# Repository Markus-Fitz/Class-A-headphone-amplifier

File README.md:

# Class-A headphone amplifier
Simple class A headphone amplifier, made to be easy to build and understand while still sounding great.
The amplifier exclusively uses through-hole components, it doesn't use any integrated circuits and it uses standard values wherever possible.

## Design Philosophy

The amplifier is designed around a simple resistor-coupled class A output stage.
I like the appeal of the simplicity of resistor-coupled output stages and it allowed the amplifier to only have one high-power active device per channel which then could be displayed.
The power-transistor is an MJ2955, chosen for its TO-3 package which I really wanted to include as a center piece of the amplifier.
The transistor comes in one format, where its collector is connected to the case of the transistor. This, in combination with its place in the schematic allows it to have a grounded case, meaning it can be put on display on the outside of the case without any danger to the user.
Unfortunately, the MJ2955 struggles to keep up with fast rise- and fall-times, which led to problems outlined in the performance section.

Preceeding the output stage, a fully discrete pre-amplifier was created to keep THD at a minimum.
It is constructed like a discrete opAmp, with a differential input section and a voltage-amplification stage that then feeds the power-stage.

The output stage is connected to the amplifier's output through capacitive coupling and a delay-board. This delay board keeps the output of the capacitors connected to ground through resistors for the first ~4 seconds, allowing the output capacitors to slowly charge. This means that the output of the capacitors are at 0 V it connects to the headphones, which avoids a "thump" when turning the amplifier on.

To keep complexity at a minimum, the amplifier is powered from a single power supply of 24V, created by an external DC power-brick.
This was done to avoid working with line voltage, keeping the amplifier safe to operate and build up for hobbyists.
The input voltage is filtered by a passive power-supply. This, again, is a nod to vintage amplifier designs and was chosen for simplicity and to avoid having more power-semiconcutors in the regulation path of the power supply boards.

## Construction

As the amplifier is constructed from separate boards, a 3D printed case was designed to screw the boards onto one single frame.
From there, they could be connected to complete the amplifier.

The case additionally houses the power- and output-switches, a potentiometer for regulating the signal coming into the amplifier and connectors for the headphone, the inputs and preamp-outputs and the power-connector.

## Performance

The amplifier works as intended and amplifies the input signal properly. The sound is okay, but heavily compromised by massive noise coupling into the output signal.
This is probably due to the wiring on the bottom of the amplifier, which brings sensitive input audio signals in close proximity of large voltages and currents of the power-supply lines and output signals.
The 3D printed case does not shield the amplifier at all, meaning that even a mobile phone's RF pings were audible loudly.

The amplifier's output-stage is limited by the slow slew-rate capability of the MJ2955 transistor. This can even be seen in the simulations, as the preamp spikes to the positive supply voltage at fast positive edges on the input signal. The MJ2955 can not switch off as fast as the preamp-section commands it to, leading to the preamp to rise positive more and more. In the simulation, replacing the MJ2955 BJT by another BD140 solves this problem completely, indicating further that the MJ2955 is to blame.

Finally, the amplifier gets very hot during operation. Initially, a 500 mA bias current through the output stage was targeted, which would have meant a 22 Ohm power resistor in the output stage. The resistance was increased to 33 Ohms due to thermal concerns and even the 33 Ohm resistor (albeit only cooled convectively) gets far too hot to touch during operation.

All in all the amplifier shows a stable operation without any unexpected oscillations or other fatal flaws. The circuit works, but has weaknesses which make it impractical in a more refined setting after the prototype stage. For this reason, a next iteration may be modified quite extensively, on the basis of the present design.

## Next steps

To adress the noise issue, the next iteration will be build as one single PCB with a continuous ground plane.
A solid case constructed of metal will provide good cooling and shielding from interference from outside signals, allowing for quiet operation and keeping the case- and amplifier-temperature in a safe region.
A thermal safety switch or electronic NTC-control circuit may be implemented for furhter safety.
The output stage will omit the MJ2955 BJT and switch to a BD140. Additionally, the resistor-coupled output stage may be exchanged in favor of a current source or even transition to class AB for more power and cooler operation.
The power-supply will most likely laso be regulated. Without the MJ2955, the argument of having only one high-power semiconductor device is moot, so a simple regulator circuit may replace the hard-to-get and unprecise LC lowpass filter.

The amplifier will still be fully discrete, fully thorugh-hole mounted and fully open-source. I really want to create something which is usable every day though and the steps above feel adequate for that.

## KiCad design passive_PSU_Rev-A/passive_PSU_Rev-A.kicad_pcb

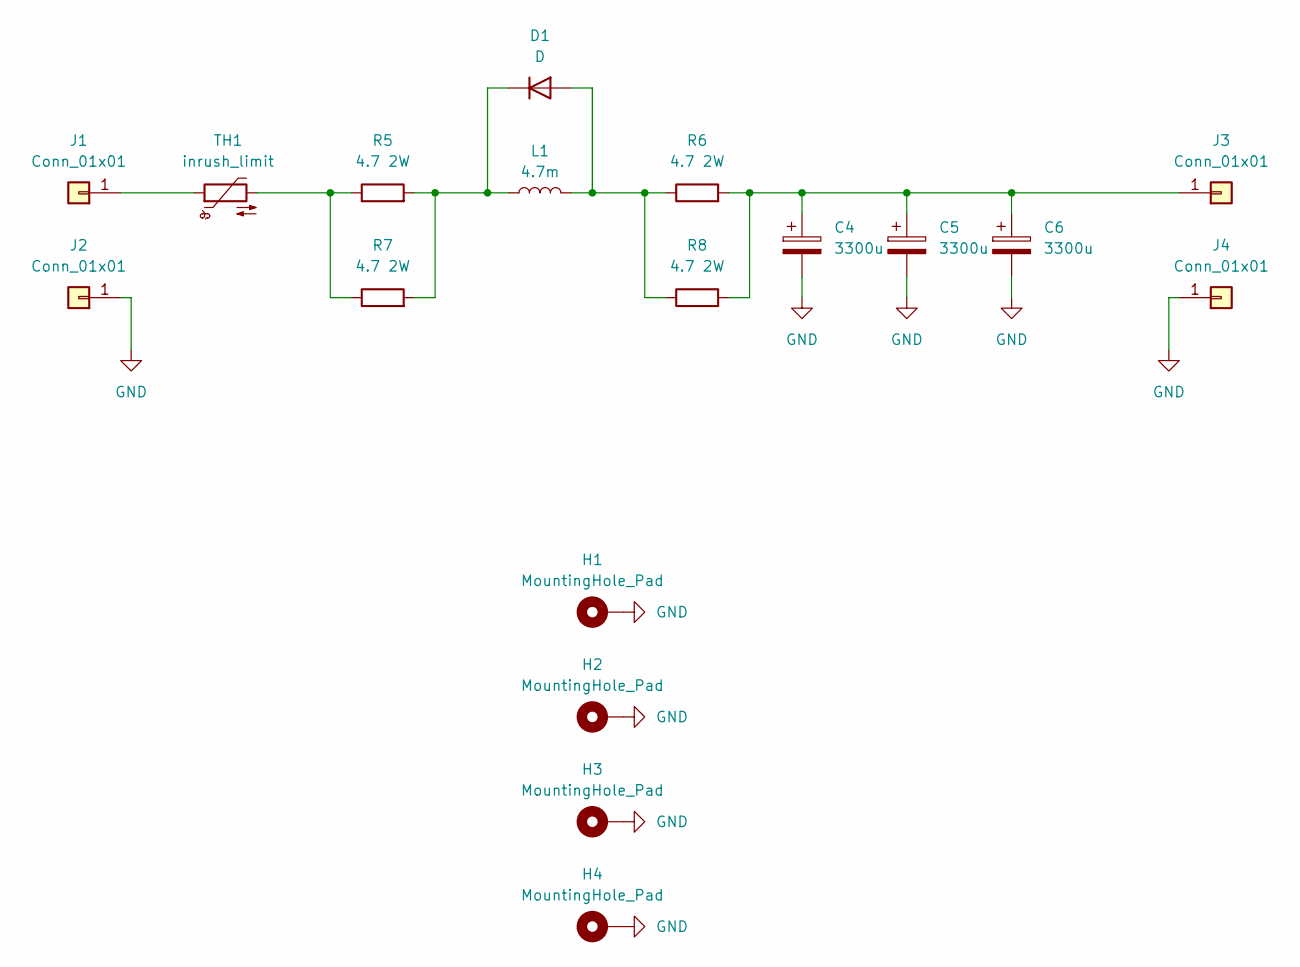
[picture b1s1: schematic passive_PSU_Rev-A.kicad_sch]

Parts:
C4, C5, C6: 3300u; CP_Radial_D16.0mm_P7.50mm; MPN UFW1V332MHD
D1: D; D_DO-27_P12.70mm_Horizontal
H1, H2, H3, H4: MountingHole_Pad; MountingHole_3.2mm_M3_DIN965_Pad_TopBottom
J1, J2, J3, J4: Conn_01x01; TestPoint_THTPad_D3.0mm_Drill1.5mm
L1: 4.7m; L_Radial_D24.4mm_P22.90mm_Murata_1400series
R5, R6, R7, R8: 4.7 2W; R_Axial_DIN0309_L9.0mm_D3.2mm_P12.70mm_Horizontal; MPN WA83ZI-4R7JT06
TH1: inrush_limit; C_Disc_D9.0mm_W5.0mm_P5.00mm; MPN B57153S0100M054

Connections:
GND: C4.2, C5.2, C6.2, H1.1, H2.1, H3.1, H4.1, J2.1, J4.1
unnamed: D1.2 (A), L1.2, R6.1, R8.1
unnamed: D1.1 (K), L1.1, R5.2, R7.2
unnamed: J1.1, TH1.1
unnamed: C4.1, C5.1, C6.1, J3.1, R6.2, R8.2
unnamed: R5.1, R7.1, TH1.2

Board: 2 copper layers, 18 parts (0 on the bottom side), 6 nets, no tracks yet.

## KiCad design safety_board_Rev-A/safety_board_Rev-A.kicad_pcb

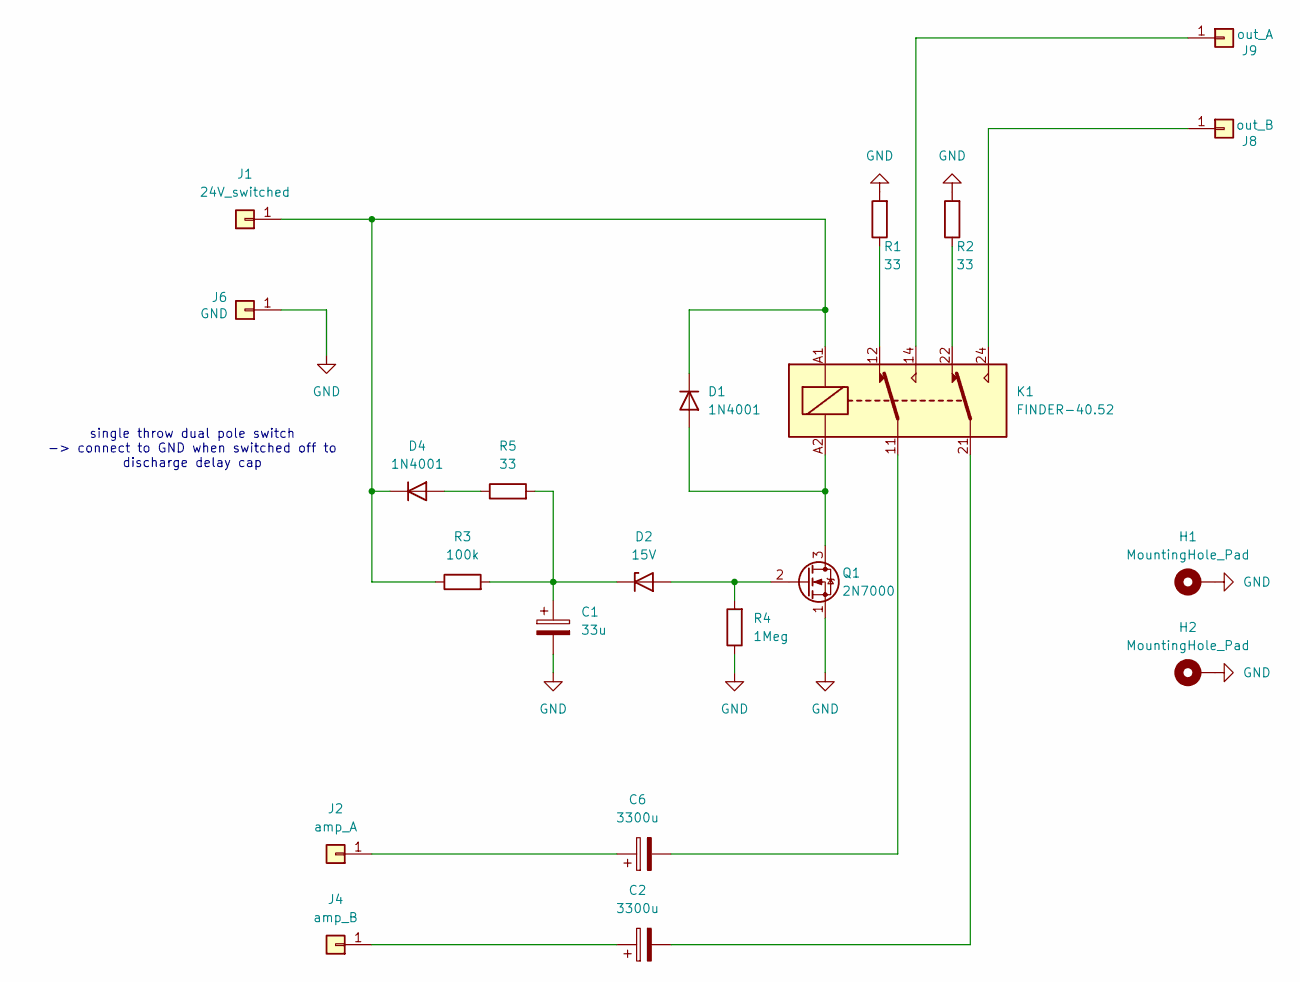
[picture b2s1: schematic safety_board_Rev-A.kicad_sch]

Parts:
C1: 33u; C_Radial_D8.0mm_H11.5mm_P3.50mm
C2, C6: 3300u; CP_Radial_D16.0mm_P7.50mm; MPN UFW1V332MHD
D1, D4: 1N4001; D_DO-41_SOD81_P10.16mm_Horizontal
D2: 15V; D_DO-35_SOD27_P7.62mm_Horizontal
H1, H2: MountingHole_Pad; MountingHole_3.2mm_M3_DIN965_Pad_TopBottom
J1: 24V_switched; TestPoint_THTPad_D3.0mm_Drill1.5mm
J2: amp_A; TestPoint_THTPad_D3.0mm_Drill1.5mm
J4: amp_B; TestPoint_THTPad_D3.0mm_Drill1.5mm
J6: GND; TestPoint_THTPad_D3.0mm_Drill1.5mm
J8: out_B; TestPoint_THTPad_D3.0mm_Drill1.5mm
J9: out_A; TestPoint_THTPad_D3.0mm_Drill1.5mm
K1: FINDER-40.52; Relay_DPDT_Finder_40.52
Q1: 2N7000; TO-92_Inline
R1, R2, R5: 33; R_Axial_DIN0207_L6.3mm_D2.5mm_P10.16mm_Horizontal
R3: 100k; R_Axial_DIN0207_L6.3mm_D2.5mm_P10.16mm_Horizontal
R4: 1Meg; R_Axial_DIN0207_L6.3mm_D2.5mm_P10.16mm_Horizontal

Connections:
GND: C1.2, H1.1, H2.1, J6.1, Q1.1 (S), R1.2, R2.2, R4.1
unnamed: C2.2, K1.21
unnamed: C6.2, K1.11
unnamed: D1.2 (A), K1.A2, Q1.3 (D)
unnamed: D1.1 (K), D4.1 (K), J1.1, K1.A1, R3.1
unnamed: D2.2 (A), Q1.2 (G), R4.2
unnamed: C1.1, D2.1 (K), R3.2, R5.2
unnamed: D4.2 (A), R5.1
unnamed: C6.1, J2.1
unnamed: C2.1, J4.1
unnamed: J8.1, K1.24
unnamed: J9.1, K1.14
unnamed: K1.12, R1.1
unnamed: K1.22, R2.1

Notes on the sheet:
single throw dual pole switch -> connect to GND when switched off to discharge delay cap

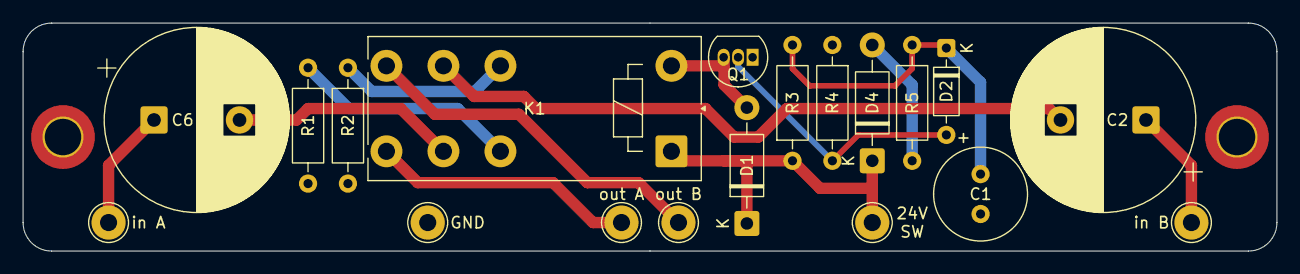
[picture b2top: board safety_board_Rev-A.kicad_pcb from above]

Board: 2 copper layers, 110.0 x 20.0 mm, 21 parts (0 on the bottom side), 14 nets.

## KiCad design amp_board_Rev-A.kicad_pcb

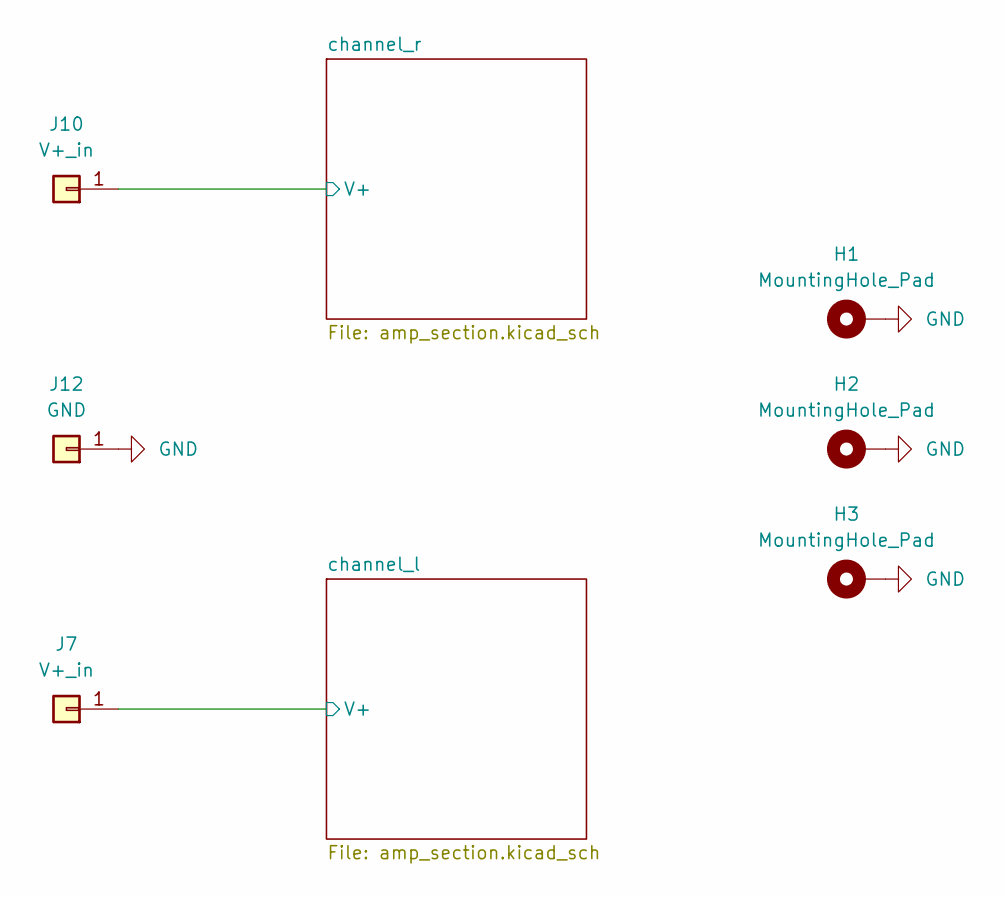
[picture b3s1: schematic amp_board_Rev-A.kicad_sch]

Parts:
H1, H2, H3: MountingHole_Pad; MountingHole_3.2mm_M3_DIN965_Pad_TopBottom
J7, J10: V+_in; TestPoint_THTPad_D3.0mm_Drill1.5mm
J12: GND; TestPoint_THTPad_D3.0mm_Drill1.5mm

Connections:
/channel_l/V+: J7.1; also elsewhere on the board
/channel_r/V+: J10.1; also elsewhere on the board
GND: H1.1, H2.1, H3.1, J12.1; also elsewhere on the board

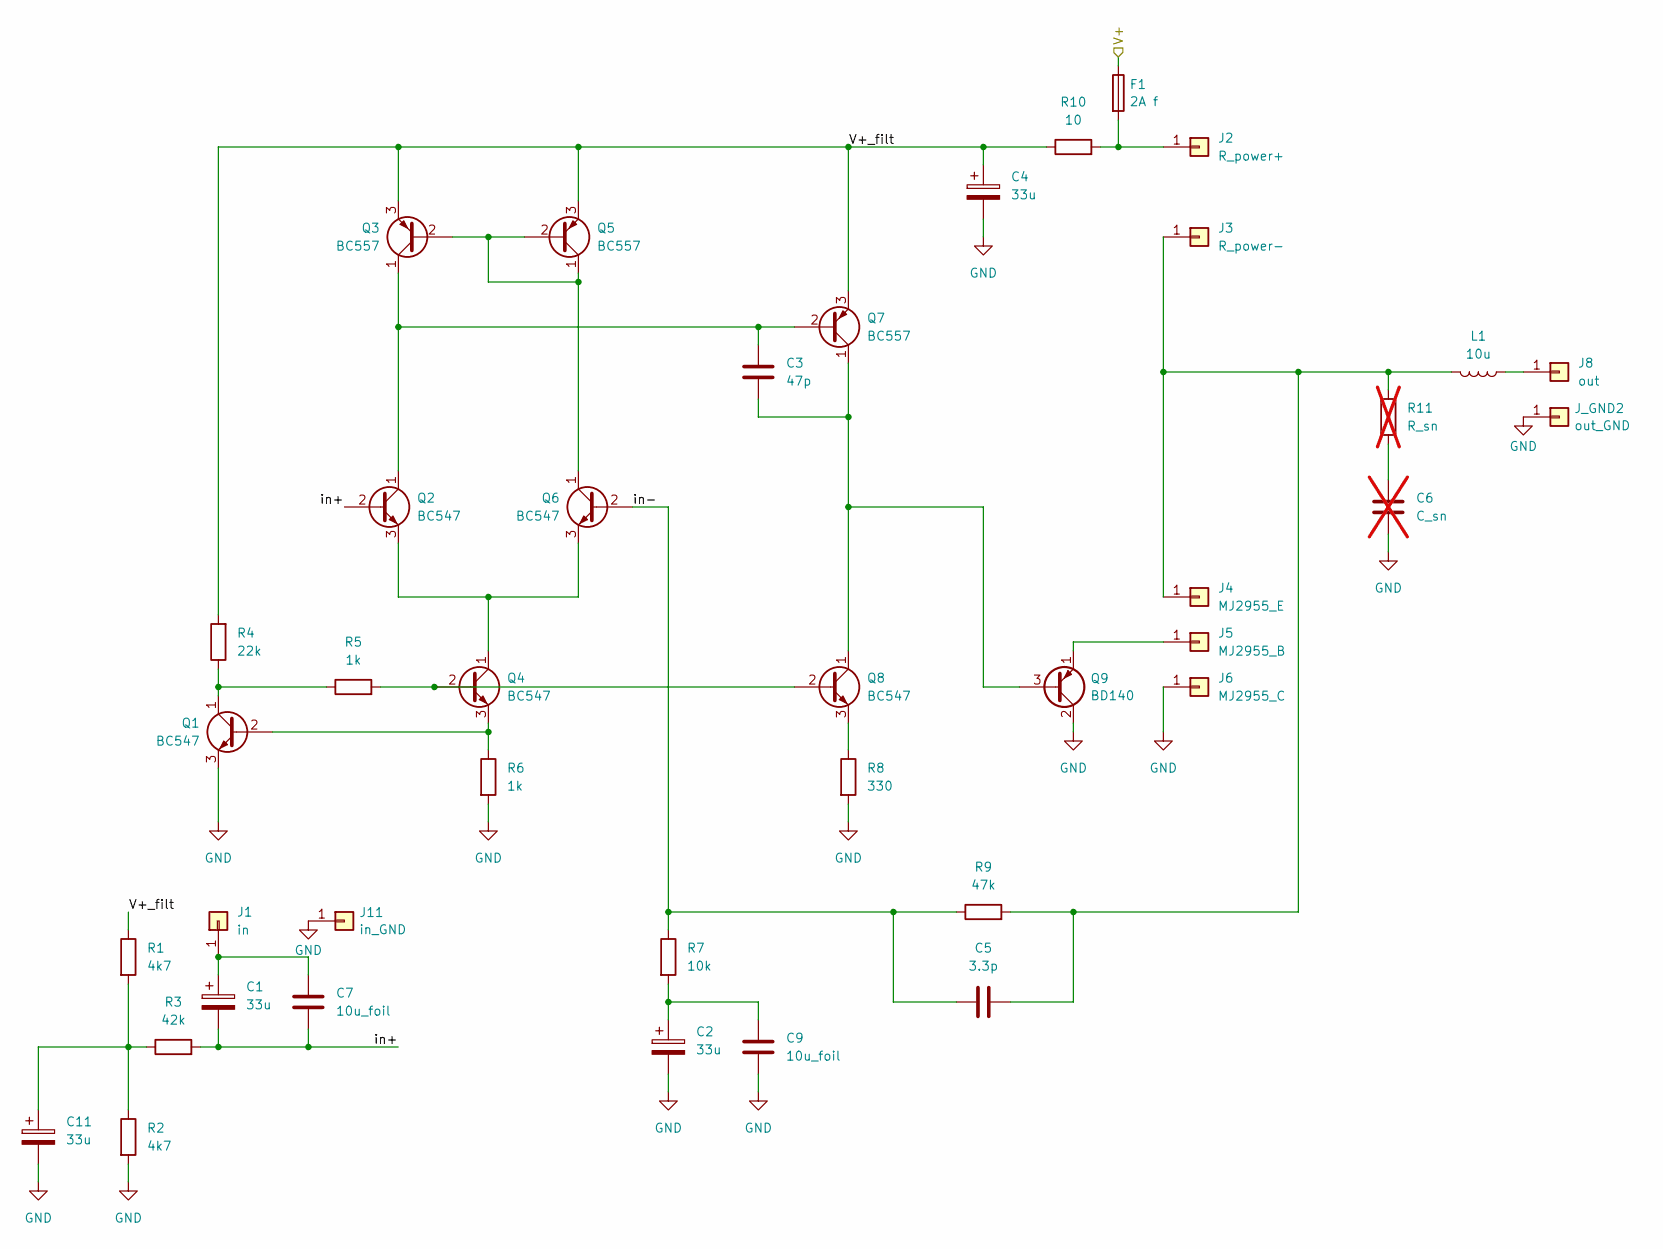
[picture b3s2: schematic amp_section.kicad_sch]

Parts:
C1, C2, C4, C11: 33u; C_Radial_D8.0mm_H11.5mm_P3.50mm
C3: 47p; C_Disc_D5.0mm_W2.5mm_P5.00mm
C5: 3.3p; C_Disc_D5.0mm_W2.5mm_P5.00mm
C6: C_sn; C_Disc_D5.0mm_W2.5mm_P5.00mm; not fitted
C7, C9: 10u_foil; C_Rect_L24.0mm_W10.9mm_P22.50mm_MKT
F1: 2A f; Fuseholder_Clip-5x20mm_Keystone_3512P_Inline_P23.62x7.27mm_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
J1: in; TestPoint_THTPad_D3.0mm_Drill1.5mm
J2: R_power+; TestPoint_THTPad_D3.0mm_Drill1.5mm
J3: R_power-; TestPoint_THTPad_D3.0mm_Drill1.5mm
J4: MJ2955_E; TestPoint_THTPad_D3.0mm_Drill1.5mm
J5: MJ2955_B; TestPoint_THTPad_D3.0mm_Drill1.5mm
J6: MJ2955_C; TestPoint_THTPad_D3.0mm_Drill1.5mm
J8: out; TestPoint_THTPad_D3.0mm_Drill1.5mm
J11: in_GND; TestPoint_THTPad_D3.0mm_Drill1.5mm
J_GND2: out_GND; TestPoint_THTPad_D3.0mm_Drill1.5mm
L1: 10u; L_Axial_L11.0mm_D4.5mm_P5.08mm_Vertical_Fastron_MECC
Q1, Q2, Q4, Q6, Q8: BC547; TO-92_Inline_Wide
Q3, Q5, Q7: BC557; TO-92_Inline_Wide
Q9: BD140; TO-126-3_Vertical
R1, R2: 4k7; R_Axial_DIN0207_L6.3mm_D2.5mm_P10.16mm_Horizontal
R3: 42k; R_Axial_DIN0207_L6.3mm_D2.5mm_P10.16mm_Horizontal
R4: 22k; R_Axial_DIN0207_L6.3mm_D2.5mm_P10.16mm_Horizontal
R5, R6: 1k; R_Axial_DIN0207_L6.3mm_D2.5mm_P10.16mm_Horizontal
R7: 10k; R_Axial_DIN0207_L6.3mm_D2.5mm_P10.16mm_Horizontal
R8: 330; R_Axial_DIN0207_L6.3mm_D2.5mm_P10.16mm_Horizontal
R9: 47k; R_Axial_DIN0207_L6.3mm_D2.5mm_P10.16mm_Horizontal
R10: 10; R_Axial_DIN0207_L6.3mm_D2.5mm_P10.16mm_Horizontal
R11: R_sn; R_Axial_DIN0207_L6.3mm_D2.5mm_P10.16mm_Horizontal; not fitted

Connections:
/channel_r/V+: F1.1; also elsewhere on the board
/channel_r/V+_filt: C4.1, Q3.3 (E), Q5.3 (E), Q7.3 (E), R1.1, R4.2, R10.1
/channel_r/in+: C1.2, C7.2, Q2.2 (B), R3.2
/channel_r/in-: C5.1, Q6.2 (B), R7.1, R9.1
GND: C2.2, C4.2, C6.2, C9.2, C11.2, J6.1, J11.1, J_GND2.1, Q1.3 (E), Q9.2 (C), R2.2, R6.2, R8.2; also elsewhere on the board
unnamed: C2.1, C9.1, R7.2
unnamed: C6.1, R11.2
unnamed: C11.1, R1.2, R2.1, R3.1
unnamed: C1.1, C7.1, J1.1
unnamed: F1.2, J2.1, R10.2
unnamed: C5.2, J3.1, J4.1, L1.2, R9.2, R11.1
unnamed: J5.1, Q9.1 (E)
unnamed: J8.1, L1.1
unnamed: Q1.2 (B), Q4.3 (E), R6.1
unnamed: Q1.1 (C), R4.1, R5.1
unnamed: C3.1, Q2.1 (C), Q3.1 (C), Q7.2 (B)
unnamed: Q2.3 (E), Q4.1 (C), Q6.3 (E)
unnamed: Q3.2 (B), Q5.1 (C), Q5.2 (B), Q6.1 (C)
unnamed: Q4.2 (B), Q8.2 (B), R5.2
unnamed: C3.2, Q7.1 (C), Q8.1 (C), Q9.3 (B)
unnamed: Q8.3 (E), R8.1

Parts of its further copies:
C8, C10: 10u_foil; C_Rect_L24.0mm_W10.9mm_P22.50mm_MKT
C12, C13, C14, C16: 33u; C_Radial_D8.0mm_H11.5mm_P3.50mm
C15: 47p; C_Disc_D5.0mm_W2.5mm_P5.00mm
C17: 3.3p; C_Disc_D5.0mm_W2.5mm_P5.00mm
C18: C_sn; C_Disc_D5.0mm_W2.5mm_P5.00mm; not fitted
F2: 2A f; Fuseholder_Clip-5x20mm_Keystone_3512P_Inline_P23.62x7.27mm_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
J_B1: MJ2955_B; TestPoint_THTPad_D3.0mm_Drill1.5mm
J_C1: MJ2955_C; TestPoint_THTPad_D3.0mm_Drill1.5mm
J_E1: MJ2955_E; TestPoint_THTPad_D3.0mm_Drill1.5mm
J_GND1: in_GND; TestPoint_THTPad_D3.0mm_Drill1.5mm
J_GND3: out_GND; TestPoint_THTPad_D3.0mm_Drill1.5mm
J_R+1: R_power+; TestPoint_THTPad_D3.0mm_Drill1.5mm
J_R-1: R_power-; TestPoint_THTPad_D3.0mm_Drill1.5mm
J_in1: in; TestPoint_THTPad_D3.0mm_Drill1.5mm
J_out1: out; TestPoint_THTPad_D3.0mm_Drill1.5mm
L3: 10u; L_Axial_L11.0mm_D4.5mm_P5.08mm_Vertical_Fastron_MECC
Q10: BD140; TO-126-3_Vertical
Q19, Q20, Q22, Q24, Q26: BC547; TO-92_Inline_Wide
Q21, Q23, Q25: BC557; TO-92_Inline_Wide
R23, R24: 4k7; R_Axial_DIN0207_L6.3mm_D2.5mm_P10.16mm_Horizontal
R25: 42k; R_Axial_DIN0207_L6.3mm_D2.5mm_P10.16mm_Horizontal
R26: 22k; R_Axial_DIN0207_L6.3mm_D2.5mm_P10.16mm_Horizontal
R27, R28: 1k; R_Axial_DIN0207_L6.3mm_D2.5mm_P10.16mm_Horizontal
R29: 10k; R_Axial_DIN0207_L6.3mm_D2.5mm_P10.16mm_Horizontal
R30: 330; R_Axial_DIN0207_L6.3mm_D2.5mm_P10.16mm_Horizontal
R31: 47k; R_Axial_DIN0207_L6.3mm_D2.5mm_P10.16mm_Horizontal
R32: 10; R_Axial_DIN0207_L6.3mm_D2.5mm_P10.16mm_Horizontal
R33: R_sn; R_Axial_DIN0207_L6.3mm_D2.5mm_P10.16mm_Horizontal; not fitted

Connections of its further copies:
/channel_l/V+: F2.1; also elsewhere on the board
/channel_l/V+_filt: C16.1, Q21.3 (E), Q23.3 (E), Q25.3 (E), R23.1, R26.2, R32.1
/channel_l/in+: C8.2, C13.2, Q20.2 (B), R25.2
/channel_l/in-: C17.1, Q24.2 (B), R29.1, R31.1
GND: C10.2, C12.2, C14.2, C16.2, C18.2, J_C1.1, J_GND1.1, J_GND3.1, Q10.2 (C), Q19.3 (E), R24.2, R28.2, R30.2; also elsewhere on the board
unnamed: C10.1, C14.1, R29.2
unnamed: C12.1, R23.2, R24.1, R25.1
unnamed: C18.1, R33.2
unnamed: J_B1.1, Q10.1 (E)
unnamed: C17.2, J_E1.1, J_R-1.1, L3.2, R31.2, R33.1
unnamed: F2.2, J_R+1.1, R32.2
unnamed: C8.1, C13.1, J_in1.1
unnamed: J_out1.1, L3.1
unnamed: C15.2, Q10.3 (B), Q25.1 (C), Q26.1 (C)
unnamed: Q19.2 (B), Q22.3 (E), R28.1
unnamed: Q19.1 (C), R26.1, R27.1
unnamed: C15.1, Q20.1 (C), Q21.1 (C), Q25.2 (B)
unnamed: Q20.3 (E), Q22.1 (C), Q24.3 (E)
unnamed: Q21.2 (B), Q23.1 (C), Q23.2 (B), Q24.1 (C)
unnamed: Q22.2 (B), Q26.2 (B), R27.2
unnamed: Q26.3 (E), R30.1

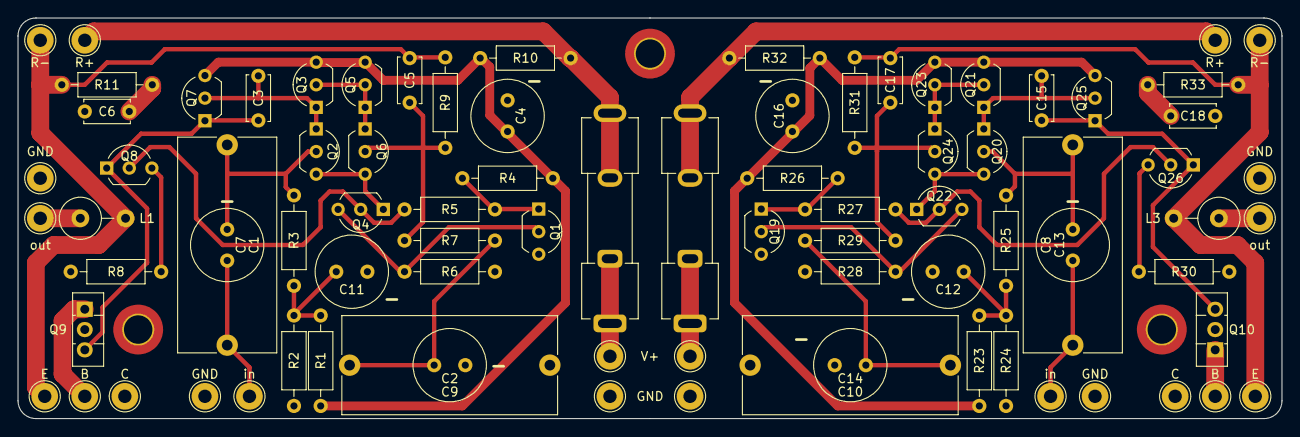
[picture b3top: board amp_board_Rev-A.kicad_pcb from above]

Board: 2 copper layers, 142.0 x 45.0 mm, 87 parts (0 on the bottom side), 41 nets.

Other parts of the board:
J9: GND; TestPoint_THTPad_D3.0mm_Drill1.5mm

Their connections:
GND: J9.1; also elsewhere on the board

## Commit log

2025-12-28 Initial upload for tidied up repository.
    New repository for cleanly uploading all files again after the structure of a previous repo got too complicated.
    This commit contains the KiCAD files for the amplifier board.
2025-12-28 Changed folder structure of previous commit.
    This commit just moves the files from the previous commit into its own folder.
2025-12-28 Commit of safety board files.
    This commit contains the safety / delay-board files responsible for a turn-on delay of the output.
    This way, the output capacitors can be charged safely without any pops or damage to connected headphones.
2025-12-28 Commit of the PCB files for the passive PSU.
    This commit contains the files for the passive PSU of the amplifier.
2026-03-01 Modified title block in schematic.
2026-03-01 Update README.md
    Updated README.
